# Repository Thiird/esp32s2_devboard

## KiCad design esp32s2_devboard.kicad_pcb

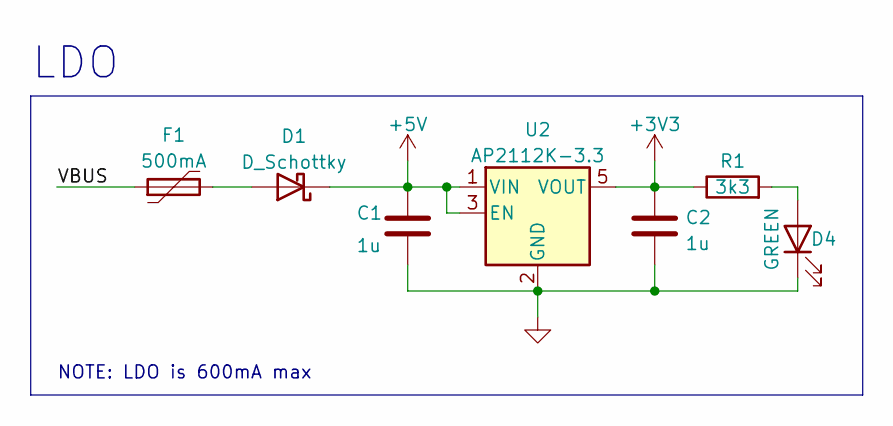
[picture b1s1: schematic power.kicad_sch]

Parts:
C1, C2: 1u; C_0603_1608Metric
D1: D_Schottky; D_0805_2012Metric
D4: GREEN; LED_0603_1608Metric
F1: 500mA; Fuse_0603_1608Metric
R1: 3k3; R_0603_1608Metric
U2: AP2112K-3.3; SOT-23-5

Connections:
+5V: C1.1, D1.1 (K), U2.1 (VIN), U2.3 (EN)
/Power/VBUS: F1.1
GND: C1.2, C2.2, D4.1 (K), U2.2 (GND); also elsewhere on the board
unnamed: D1.2 (A), F1.2
unnamed: D4.2 (A), R1.2

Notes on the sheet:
NOTE: LDO is 600mA max
LDO

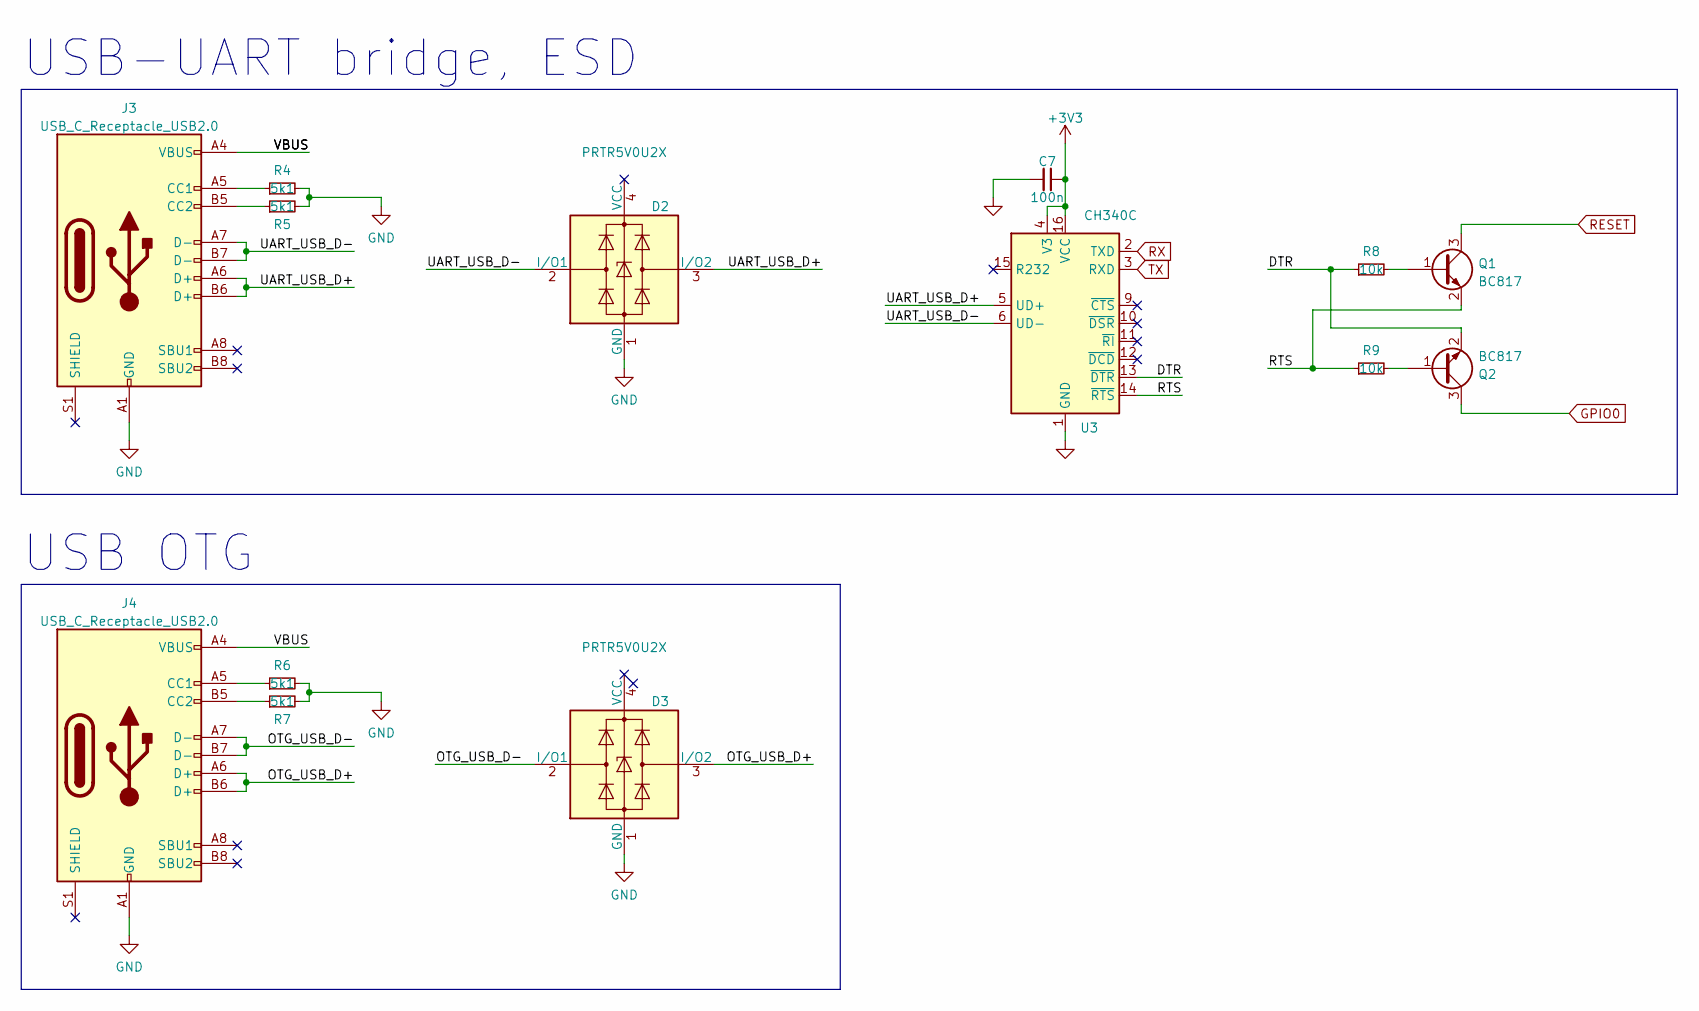
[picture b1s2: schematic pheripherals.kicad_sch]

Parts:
C7: 100n; C_0603_1608Metric
D2, D3: PRTR5V0U2X; SOT-143
J3, J4: USB_C_Receptacle_USB2.0; USB_C_Receptacle_HRO_TYPE-C-31-M-12
Q1, Q2: BC817; SOT-23
R4, R5, R6, R7: 5k1; R_0603_1608Metric
R8, R9: 10k; R_0603_1608Metric
U3: CH340C; SOIC-16_3.9x9.9mm_P1.27mm

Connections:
/Pheripherals/DTR: Q2.2 (E), R8.1, U3.13 (~DTR)
/Pheripherals/OTG_USB_D+: D3.3 (I/O2), J4.A6 (D+), J4.B6 (D+)
/Pheripherals/OTG_USB_D-: D3.2 (I/O1), J4.A7 (D-), J4.B7 (D-)
/Pheripherals/RTS: Q1.2 (E), R9.1, U3.14 (~RTS)
/Pheripherals/UART_USB_D+: D2.3 (I/O2), J3.A6 (D+), J3.B6 (D+), U3.5 (UD+)
/Pheripherals/UART_USB_D-: D2.2 (I/O1), J3.A7 (D-), J3.B7 (D-), U3.6 (UD-)
/Pheripherals/VBUS: J3.A4 (VBUS), J3.A9 (VBUS), J3.B4 (VBUS), J3.B9 (VBUS), J4.A4 (VBUS), J4.A9 (VBUS), J4.B4 (VBUS), J4.B9 (VBUS)
GND: C7.2, D2.1 (GND), D3.1 (GND), J3.A1 (GND), J3.A12 (GND), J3.B1 (GND), J3.B12 (GND), J4.A1 (GND), J4.A12 (GND), J4.B1 (GND), J4.B12 (GND), R4.2, R5.2, R6.2, R7.2, U3.1 (GND); also elsewhere on the board
GPIO0: Q2.3 (C); also elsewhere on the board
unnamed: J3.A5 (CC1), R4.1
unnamed: J3.B5 (CC2), R5.1
unnamed: J4.A5 (CC1), R6.1
unnamed: J4.B5 (CC2), R7.1
unnamed: Q1.1 (B), R8.2
unnamed: Q2.1 (B), R9.2
RESET: Q1.3 (C); also elsewhere on the board
RX: U3.2 (TXD); also elsewhere on the board
TX: U3.3 (RXD); also elsewhere on the board

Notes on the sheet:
USB OTG
USB-UART bridge, ESD

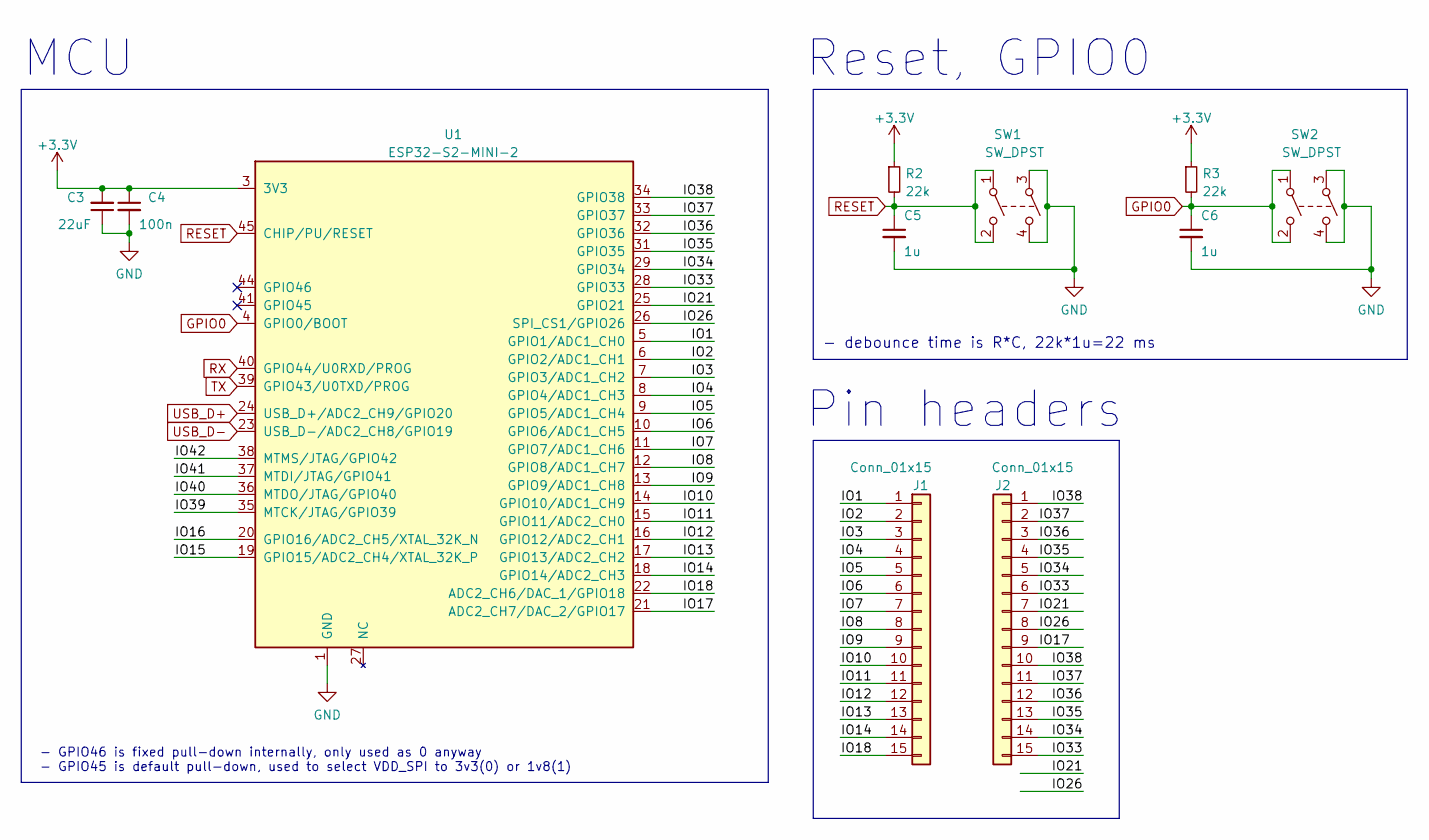
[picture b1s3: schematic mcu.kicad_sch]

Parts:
C3: 22uF; C_0603_1608Metric
C4: 100n; C_0603_1608Metric
C5, C6: 1u; C_0603_1608Metric
J1, J2: Conn_01x15; PinHeader_1x15_P2.54mm_Vertical
R2, R3: 22k; R_0603_1608Metric
SW1, SW2: SW_DPST; SW_SKRPACE010
U1: ESP32-S2-MINI-2; ESP32-S2-MINI-1

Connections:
/MCU/IO1: J1.1, U1.5 (GPIO1/ADC1_CH0)
/MCU/IO2: J1.2, U1.6 (GPIO2/ADC1_CH1)
/MCU/IO3: J1.3, U1.7 (GPIO3/ADC1_CH2)
/MCU/IO4: J1.4, U1.8 (GPIO4/ADC1_CH3)
/MCU/IO5: J1.5, U1.9 (GPIO5/ADC1_CH4)
/MCU/IO6: J1.6, U1.10 (GPIO6/ADC1_CH5)
/MCU/IO7: J1.7, U1.11 (GPIO7/ADC1_CH6)
/MCU/IO8: J1.8, U1.12 (GPIO8/ADC1_CH7)
/MCU/IO9: J1.9, U1.13 (GPIO9/ADC1_CH8)
/MCU/IO10: J1.10, U1.14 (GPIO10/ADC1_CH9)
/MCU/IO11: J1.11, U1.15 (GPIO11/ADC2_CH0)
/MCU/IO12: J1.12, U1.16 (GPIO12/ADC2_CH1)
/MCU/IO13: J1.13, U1.17 (GPIO13/ADC2_CH2)
/MCU/IO14: J1.14, U1.18 (GPIO14/ADC2_CH3)
/MCU/IO15: U1.19 (GPIO15/ADC2_CH4/XTAL_32K_P)
/MCU/IO16: U1.20 (GPIO16/ADC2_CH5/XTAL_32K_N)
/MCU/IO17: J2.9, U1.21 (ADC2_CH7/DAC_2/GPIO17)
/MCU/IO18: J1.15, U1.22 (ADC2_CH6/DAC_1/GPIO18)
/MCU/IO21: J2.7, U1.25 (GPIO21)
/MCU/IO26: J2.8, U1.26 (SPI_CS1/GPIO26)
/MCU/IO33: J2.6, J2.15, U1.28 (GPIO33)
/MCU/IO34: J2.5, J2.14, U1.29 (GPIO34)
/MCU/IO35: J2.4, J2.13, U1.31 (GPIO35)
/MCU/IO36: J2.3, J2.12, U1.32 (GPIO36)
/MCU/IO37: J2.2, J2.11, U1.33 (GPIO37)
/MCU/IO38: J2.1, J2.10, U1.34 (GPIO38)
/MCU/IO39: U1.35 (MTCK/JTAG/GPIO39)
/MCU/IO40: U1.36 (MTDO/JTAG/GPIO40)
/MCU/IO41: U1.37 (MTDI/JTAG/GPIO41)
/MCU/IO42: U1.38 (MTMS/JTAG/GPIO42)
GND: C3.1, C4.2, C5.2, C6.2, SW1.3, SW1.4, SW2.3, SW2.4, U1.1 (GND), U1.2 (GND), U1.30 (GND), U1.42 (GND), U1.43 (GND), U1.46 (GND), U1.47 (GND), U1.48 (GND), U1.49 (GND), U1.50 (GND), U1.51 (GND), U1.52 (GND), U1.53 (GND), U1.54 (GND), U1.55 (GND), U1.56 (GND), U1.57 (GND), U1.58 (GND), U1.59 (GND), U1.60 (GND), U1.61 (GND), U1.62 (GND), U1.63 (GND), U1.64 (GND), U1.65 (GND); also elsewhere on the board
GPIO0: C6.1, R3.2, SW2.1, SW2.2, U1.4 (GPIO0/BOOT); also elsewhere on the board
RESET: C5.1, R2.2, SW1.1, SW1.2, U1.45 (CHIP/PU/RESET); also elsewhere on the board
RX: U1.40 (GPIO44/U0RXD/PROG); also elsewhere on the board
TX: U1.39 (GPIO43/U0TXD/PROG); also elsewhere on the board
USB_D+: U1.24 (USB_D+/ADC2_CH9/GPIO20)
USB_D-: U1.23 (USB_D-/ADC2_CH8/GPIO19)

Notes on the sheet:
- debounce time is R*C, 22k*1u=22 ms
Pin headers
MCU
Reset, GPIO0
- GPIO46 is fixed pull-down internally, only used as 0 anyway - GPIO45 is default pull-down, used to select VDD_SPI to 3v3(0) or 1v8(1)

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
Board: 2 copper layers, 32 parts (17 on the bottom side), 46 nets, no tracks yet.

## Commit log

2022-11-21 First commit. I have to do a dev board for eveery MCU possible
2022-11-30 Added sch scheets, project on hold
